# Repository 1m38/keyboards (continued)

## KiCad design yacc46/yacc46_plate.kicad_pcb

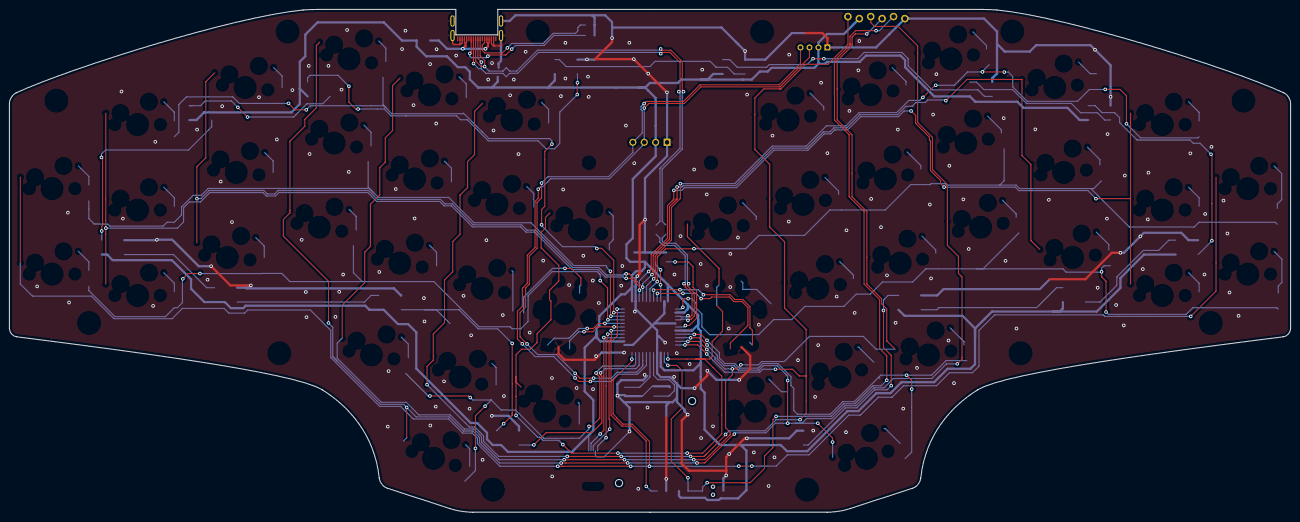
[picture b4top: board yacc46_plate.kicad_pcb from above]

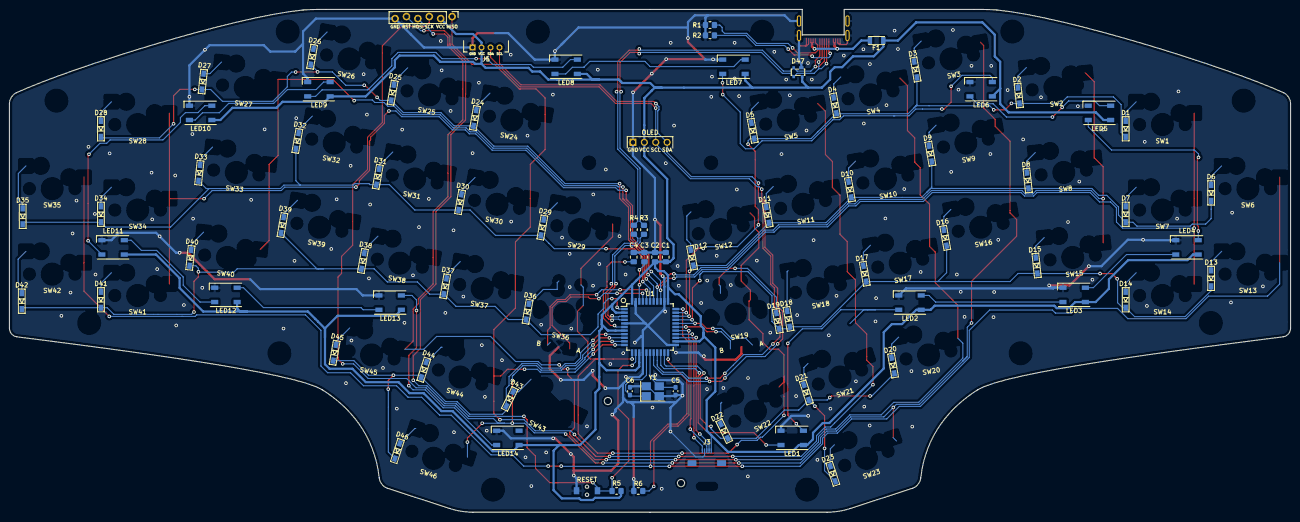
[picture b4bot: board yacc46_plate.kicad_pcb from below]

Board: 2 copper layers, 285.5 x 112.1 mm, 144 parts (79 on the bottom side), 45 nets.

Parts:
C1: 10u; C_0805_2012Metric_Pad1.18x1.45mm_HandSolder
C2, C3: 0.1u; C_0805_2012Metric_Pad1.18x1.45mm_HandSolder
C4: 1u; C_0805_2012Metric_Pad1.18x1.45mm_HandSolder
C5, C6: 22p; C_0603_1608Metric_Pad1.08x0.95mm_HandSolder
D1, D2, D3, D4, D5, D6, D7, D8, D9, D10, D11, D12, D13, D14, D15, D16, D17, D18, D19, D20, D21, D22, D23, D24, D25, D26, D27, D28, D29, D30, D31, D32, D33, D34, D35, D36, D37, D38, D39, D40, D41, D42, D43, D44, D45, D46: D; D3_SMD_v2_silk
D47: PRTR5V0U2X; PRTR5V0U2X_SOT143B
F1: 500mA; Bouns_PTC_ResettableFuse
H1, H2, H3, H4, H5, H6, H7, H8, H9, H10, H11, H12, H13, H14: MountingHole; M2_ScrewHole
HOLE_ST: Switch_Joycon_Joystick_FPC_hole
J1: USB_C_Receptacle_USB2.0; USB-C_Female_CX90M-16P
J2: OLED_I2C; OLED-0.96in
J3: joystick_switch_joycon; Molex_FPC_CON_0.5mm_5pin_5051100592
J4: AVR-ISP-6; ICSP-Header-ZigZag-Single
J5: GLOVE_I2C; Grove_I2C
LED1, LED2, LED3, LED4, LED5, LED6, LED7, LED8, LED9, LED10, LED11, LED12, LED13, LED14: WS2812B; LED_WS2812B-PLCC4
R1, R2: 5.1k; R_0805_2012Metric_Pad1.20x1.40mm_HandSolder
R3, R4: 22; R_0805_2012Metric_Pad1.20x1.40mm_HandSolder
R5, R6: 10k; R_0805_2012Metric_Pad1.20x1.40mm_HandSolder
ST1: Switch_Joycon_Joystick
SW1, SW2, SW3, SW4, SW5, SW6, SW7, SW8, SW9, SW10, SW11, SW12, SW13, SW14, SW15, SW16, SW17, SW18, SW20, SW21, SW22, SW23, SW24, SW25, SW26, SW27, SW28, SW29, SW30, SW31, SW32, SW33, SW34, SW35, SW37, SW38, SW39, SW40, SW41, SW42, SW43, SW44, SW45, SW46: SW_PUSH; CherryMX_SwitchHole_RoundCorner
SW19, SW36: Rotary_Encoder_Switch; EC11E-and-CherryMX_SwitchHole_RoundCorner
SW47: SW_Push; SW_PUSH_SMD_TVAF06-A020B-R_HandSolder
U1: ATmega32U4-AU; TQFP-44_10x10mm_P0.8mm
Y1: 16MHz; Crystal_SMD_SeikoEpson_FA238-4Pin_3.2x2.5mm_HandSoldering

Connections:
AREF: C3.1, U1.42
COL3: J4.3, U1.9
COL4: J4.4, U1.10
COL5: J4.1, U1.11
DN: R3.1, U1.3
DP: R4.1, U1.4
GND: C1.1, C2.1, C3.2, C4.2, C5.2, C6.2, D47.1, J1.A1, J1.A12, J1.B1, J1.B12, J1.S1, J2.1, J3.2, J4.6, J5.4, LED1.3, LED2.3, LED3.3, LED4.3, LED5.3, LED6.3, LED7.3, LED8.3, LED9.3, LED10.3, LED11.3, LED12.3, LED13.3, LED14.3, R1.2, R2.1, R6.1, SW47.1, U1.5, U1.15, U1.23, U1.35, U1.43, Y1.2, Y1.4
HWB: R6.2, U1.33
JOYSTBT: J3.3, U1.27
JOYSTX: J3.1, U1.26
JOYSTY: J3.4, U1.25
LED: LED1.4, U1.20
unnamed: J1.A5, R1.1
unnamed: J1.B5, R2.2
unnamed: LED1.2, LED2.4
unnamed: LED2.2, LED3.4
unnamed: LED3.2, LED4.4
unnamed: LED4.2, LED5.4
unnamed: LED5.2, LED6.4
unnamed: LED6.2, LED7.4
unnamed: LED7.2, LED8.4
unnamed: LED8.2, LED9.4
unnamed: LED10.2, LED11.4
unnamed: LED9.2, LED10.4
unnamed: LED11.2, LED12.4
unnamed: LED12.2, LED13.4
unnamed: LED13.2, LED14.4
RESET: J4.5, R5.2, SW47.2, U1.13
ROWL0: D1.1, D2.1, D3.1, D4.1, D5.1, U1.32
ROWL1: D6.1, D7.1, D8.1, D9.1, D10.1, D11.1, D12.1, U1.31
ROWL2: D13.1, D14.1, D15.1, D16.1, D17.1, D18.1, D19.1, U1.30
ROWL3: D20.1, D21.1, D22.1, D23.1, U1.21
ROWR0: D24.1, D25.1, D26.1, D27.1, D28.1, U1.38
ROWR1: D29.1, D30.1, D31.1, D32.1, D33.1, D34.1, D35.1, U1.39
ROWR2: D36.1, D37.1, D38.1, D39.1, D40.1, D41.1, D42.1, U1.1
ROWR3: D43.1, D44.1, D45.1, D46.1, U1.8
SCL: J2.3, J5.2, U1.18
SDA: J2.4, J5.1, U1.19
UCAP: C4.1, U1.6
UDN: D47.3, J1.A7, J1.B7, R3.2
UDP: D47.2, J1.A6, J1.B6, R4.2
UVBUS: F1.2, J1.A4, J1.A9, J1.B4, J1.B9
VBUS: C1.2, C2.2, D47.4, F1.1, J2.2, J3.5, J4.2, J5.3, LED1.1, LED2.1, LED3.1, LED4.1, LED5.1, LED6.1, LED7.1, LED8.1, LED9.1, LED10.1, LED11.1, LED12.1, LED13.1, LED14.1, R5.1, U1.2, U1.7, U1.14, U1.24, U1.34, U1.44
XTAL1: C5.1, U1.17, Y1.3
XTAL2: C6.1, U1.16, Y1.1

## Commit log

2020-09-06 基板作成、キー配置スクリプト作成
2020-09-06 ライブラリの参照を修正
2020-09-07 回路図を更新
    - Grove I2C端子用ホールを追加
    - LEDテープ用接点を追加
2020-09-08 輪郭線を追加
2020-09-08 一部パーツを配置
2020-09-08 LEDを2つ追加
2020-09-08 オートルータ準備
2020-09-13 仮配線・Mounting Hole追加
2020-09-13 一旦配線を完了
2020-09-13 配線完了
2020-09-14 シルク調整中
2020-09-14 oled用ネジ穴追加、各種調整、クレジット追加
2020-09-14 プロジェクト名をリネーム
2020-09-14 基板外形を変更
2020-09-14 トッププレートを作成(USB, TRRSコネクタ未カット)
2020-09-15 USBコネクタをCX70M-24P1に変更
2020-09-17 おおよそPCBの最終調整完了
2020-09-17 v0.1発注データ
2020-09-18 プレートデータを作成
2020-10-04 make yacc46 directory
2020-10-04 add kicad libraries as submodules
2020-10-04 add 1m38_kbd footprint library
2020-10-04 setup project local libraries
2020-10-04 add LICENSE
2020-10-04 リセットスイッチ・水晶のフットプリントを変更
2020-10-05 ロータリーエンコーダ部分のスイッチをMillMaxソケットに対応
    スイッチ用スルーホールを直径1.6mmに変更
2020-10-12 OLEDのフットプリントを修正
2020-10-12 配線を修正
2020-11-01 フットプリントを修正
2020-11-06 key_arrange.pyを変更、フットプリントの位置を微調整
2020-11-08 GND配線を修正
2020-11-08 クレジットを追加
2020-11-11 GND viaを追加
2020-11-11 GND, USB配線を修正
2020-11-12 基板を調整
2020-11-12 v0.2発注データ
2020-11-14 v0.1 plateデータのディレクトリを変更
2020-11-18 プレート元データを作成
2020-11-18 プレートデータ(Sandwich)を作成
2020-11-23 ロータリーエンコーダ兼用スイッチ穴のフットプリントを修正
2020-11-23 プレートデータ(Sandwitch)を修正
2021-02-21 update submodules
2021-03-07 yacc46の回路図を修正
    - ESD保護ダイオードPRTR5V0U2Xを追加
    - USBレセプタクルをCX90M-16Pに変更
    - LEDをWS2812Bに変更
    - MountingHoleを追加
2021-03-07 yacc46 PCB: MountingHoleを修正
    - 中央の穴を削除
    - リファレンスを修正
2021-03-07 yacc46 回路図: LED13,14を忘れていたので追加
2021-05-10 yacc46 回路図: Switchジョイコンのジョイスティックを追加 (ピン配置は仮)
2021-05-10 FPCコネクタのフットプリントを作成
2021-05-10 ジョイコン本体のフットプリントを作成
2021-05-10 フットプリント追加・ジョイコン用にキー配置スクリプトを調整
2021-05-11 ESDダイオードのフットプリントを変更
2021-05-11 [WIP]仮配置
2021-05-11 基板外形を変更
    ジョイコン配置によって横幅が広がったので、ついでに基板外形を引き直した
2021-05-15 [WIP]配線中
2021-05-23 v0.3発注版
2021-05-30 sandwitchプレートデータを作成
2021-05-30 sandwitchプレートデータを分割
2021-06-28 update v0.3 plate data
    add sandwitch/top_grove (top plate with grove connector space)
2021-06-28 update yacc46 schematic and footprints
2021-06-28 PCB edge
2021-06-28 modify hole and LED positions
2021-06-28 modify diode positions
2021-08-28 update yacc46 schematic
2021-09-05 arrange keyswitches
2021-09-11 update edge (shorten the width)
2021-09-11 modify leds and holes position
2021-09-11 revert keyswitch footprint
2021-09-11 flip right hand side's diodes direction
2021-09-12 modify led positions
2021-09-12 modify PCB design rules
2021-09-12 partially wired
2021-09-12 modify footprint of rotary encoders (use hot-swap socket)
2021-09-12 modify hole positions
2021-09-12 wire PCB
2021-09-12 add logo
2021-09-19 move cover-plate screw hole
2021-09-19 create PCB top-plate data
2021-09-19 move v0.3 plate data
2021-09-21 garver files
2021-09-26 modify some Edge.Cuts layer footprints
2021-09-26 move directory of plate_v0.4 pcb project
2021-09-26 plate svg data
2021-09-30 add schema.pdf
2021-10-03 yacc46 VIA definition
2021-10-12 enable to change encoders' action with VIA
2021-10-16 add build guide
2021-10-17 yacc46 v0.4 full-scale drawing
2021-10-17 add yacc46 readme.md
2021-10-17 modify buildguide
2021-10-21 update buildguide
2021-10-23 move some diodes
2021-10-23 add row/col number silks
2021-10-23 modify some wiring
2021-10-29 yacc46 v1.0 garver
2021-10-29 yacc46 v1.0 plate: add copper on the back side
2021-10-29 rename plate data v0.4 -> v1.0
2021-10-29 add readme for plate data
2021-10-29 add revision to schema.pdf
2022-04-03 create cp16 project, Seeed XIAO RP2040 symbol & footprint
2022-04-03 cp16 schematic[WIP/キースイッチのフットプリント割当がまだ]
2022-04-08 Layout parts
2022-04-11 Routing
2022-04-13 cp16 plate PCB
2022-04-16 create garver files
